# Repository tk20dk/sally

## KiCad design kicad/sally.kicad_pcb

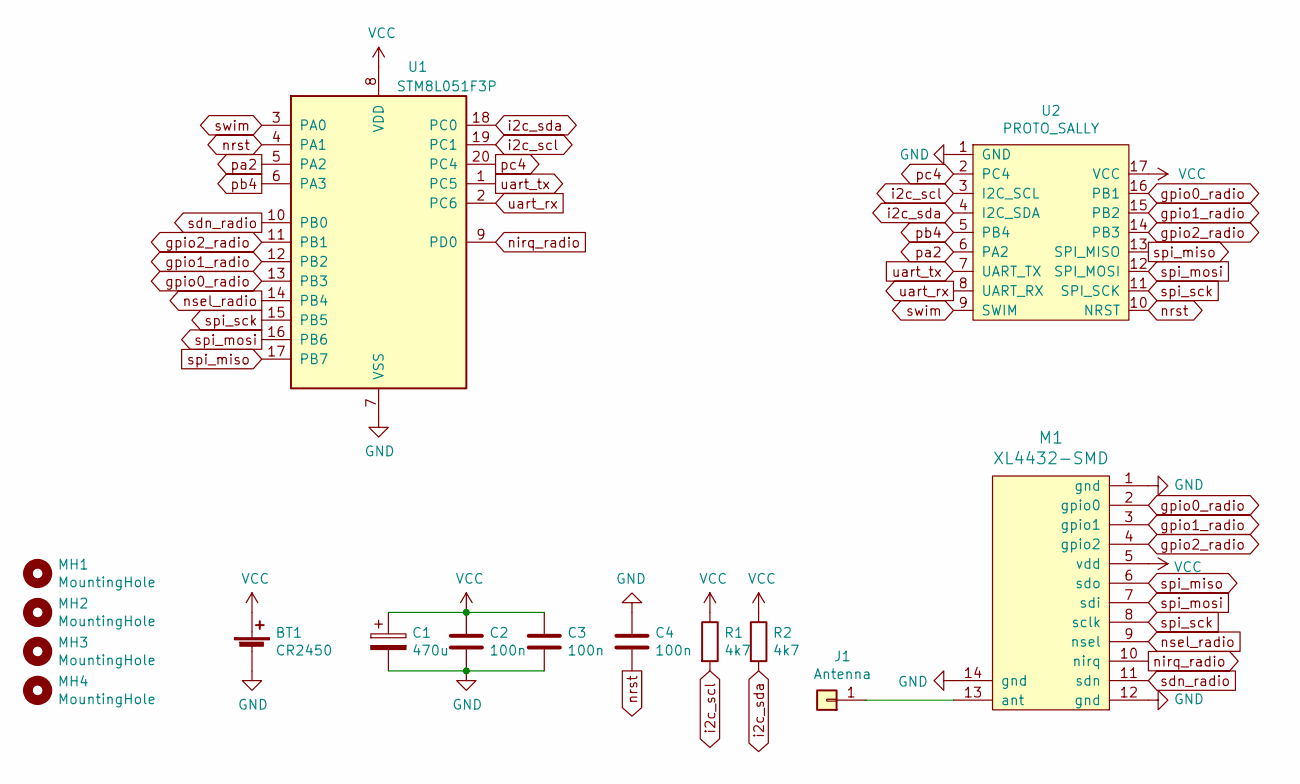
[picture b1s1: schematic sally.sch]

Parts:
BT1: CR2450; CR2450H
C1: 470u; CP_EIA-7343-15_Kemet-W
C2, C3, C4: 100n; C_0603_1608Metric
J1: Antenna; PinHeader_1x01_P2.54mm_Vertical
M1: XL4432-SMD; RF4462PRO
MH1, MH2, MH3, MH4: MountingHole; MountingHole_2.5mm
R1, R2: 4k7; R_0603_1608Metric
U1: STM8L051F3P; TSSOP-20_4.4x6.5mm_P0.65mm
U2: PROTO_SALLY

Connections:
GND: BT1.2 (-), C1.2, C2.2, C3.2, C4.1, M1.1 (gnd), M1.12 (gnd), M1.14 (gnd), U1.7 (VSS), U2.1 (GND)
unnamed: J1.1, M1.13 (ant)
VCC: BT1.1 (+), C1.1, C2.1, C3.1, M1.5 (vdd), R1.1, R2.1, U1.8 (VDD), U2.17 (VCC)
gpio0_radio: M1.2 (gpio0), U1.13 (PB3), U2.16 (PB1)
gpio1_radio: M1.3 (gpio1), U1.12 (PB2), U2.15 (PB2)
gpio2_radio: M1.4 (gpio2), U1.11 (PB1), U2.14 (PB3)
i2c_scl: R1.2, U1.19 (PC1), U2.3 (I2C_SCL)
i2c_sda: R2.2, U1.18 (PC0), U2.4 (I2C_SDA)
nirq_radio: M1.10 (nirq), U1.9 (PD0)
nrst: C4.2, U1.4 (PA1), U2.10 (NRST)
nsel_radio: M1.9 (nsel), U1.14 (PB4)
pa2: U1.5 (PA2), U2.6 (PA2)
pb4: U1.6 (PA3), U2.5 (PB4)
pc4: U1.20 (PC4), U2.2 (PC4)
sdn_radio: M1.11 (sdn), U1.10 (PB0)
spi_miso: M1.6 (sdo), U1.17 (PB7), U2.13 (SPI_MISO)
spi_mosi: M1.7 (sdi), U1.16 (PB6), U2.12 (SPI_MOSI)
spi_sck: M1.8 (sclk), U1.15 (PB5), U2.11 (SPI_SCK)
swim: U1.3 (PA0), U2.9 (SWIM)
uart_rx: U1.2 (PC6), U2.8 (UART_RX)
uart_tx: U1.1 (PC5), U2.7 (UART_TX)

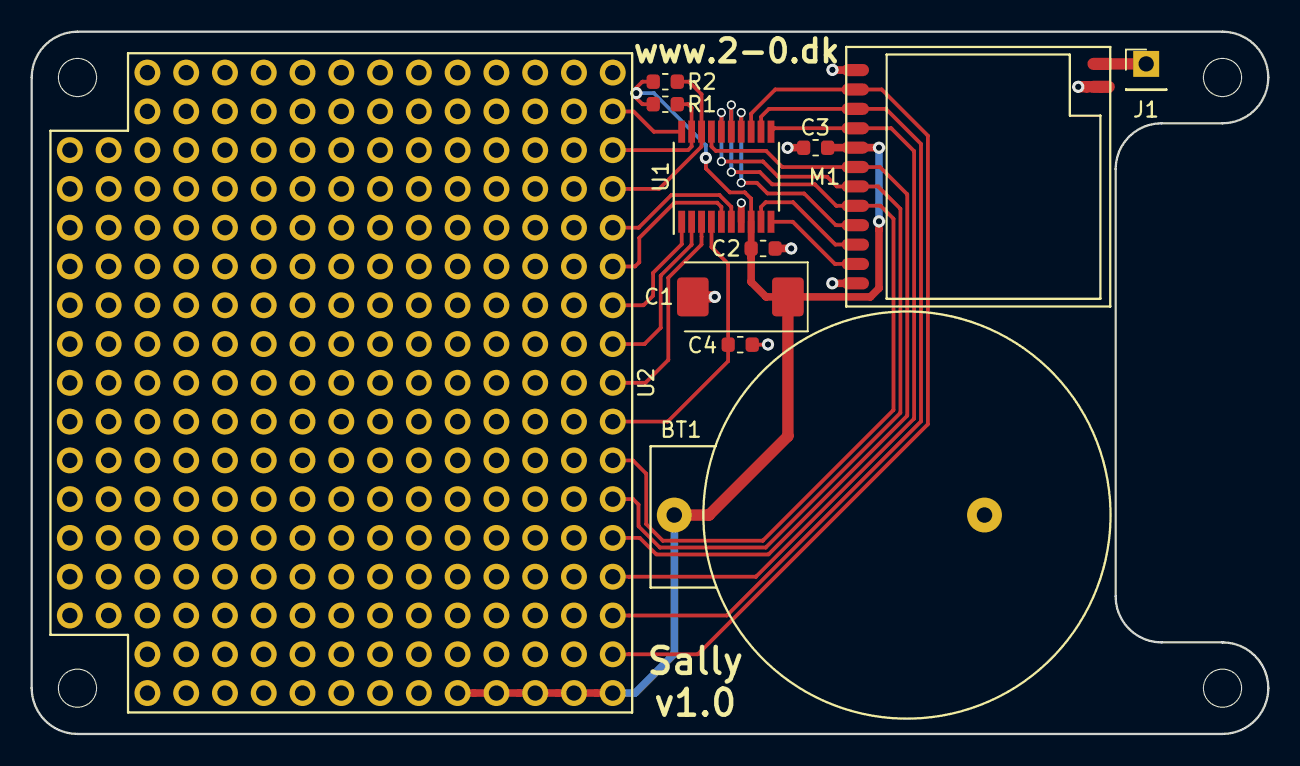
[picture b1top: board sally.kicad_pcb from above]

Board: 2 copper layers, 81.0 x 46.0 mm, 15 parts (0 on the bottom side), 21 nets.

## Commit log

2020-11-19 created initial kicad and stm8 projects
